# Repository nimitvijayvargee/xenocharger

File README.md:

# xenocharger
xenocharger is a compact 15.24mm x 15.24mm (0.6mil x 0.6mil) lipo charger and regulator packed with a ton of features! it can charge a battery 500mA, power projects up to 600mA on 3.3V, with features such as DPPM and trickle charging! It's powered by the BQ24030 IC and TP63001 from TI.

## PCB
the PCB is a compact 2 layer board that uses castellated holes to save even more spaces. 4 sets of headers are broken out, one for the battery, one for the input, one for the output and one for charge status.

## BOM
This is a rough BOM for the costs for this project. A PCB BOM can be found in pcb/prod/bom.csv, and the project BOM is just BOM.csv in the root of this repository.

ICs 
- TPS63001
- BQ24030

Other
- 1x BAT60A Diode

Passives
- 4x 100nF 0402
- 1x 1uF 0402
- 5x 10uF 0402
- 2x 22uF X7R 0402
- 1x 10kOhm 0402
- 1x 2.2kOhm 0402
- 1x 36kOhm 0402
- 1x 100Ohm 0402
- 1x SWPA3015S2R2MT 2.2uH

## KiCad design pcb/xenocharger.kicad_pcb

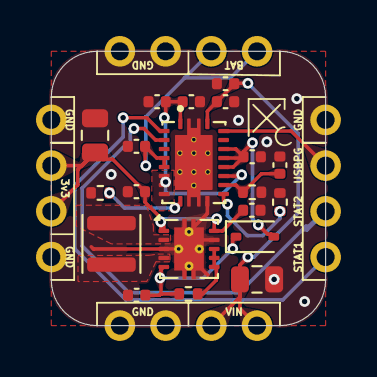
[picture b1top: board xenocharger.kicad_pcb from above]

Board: 2 copper layers, 15.2 x 15.2 mm, 24 parts (0 on the bottom side), 16 nets.

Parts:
C1, C2: X7R 22u; C_0805_2012Metric
C3, C4, C5, C9, C11: 10u; C_0402_1005Metric
C6, C7, C10, C12: 100n; C_0402_1005Metric
C8: 1u; C_0402_1005Metric
D2: BAT60A; D_SOD-323
J1, J2, J3, J4: Conn_01x04; PinHeader_1x04_P2.54mm_Vertical
L1: 2.2uH; L_Sunlord_SWPA3015S
R1: 100; R_0402_1005Metric
R2: 2.2k; R_0402_1005Metric
R4: 37k; R_0402_1005Metric
R5: 10k; R_0402_1005Metric
U2: BQ24030RHLR; IC_MSP430FR2522IRHLR
U3: TPS63001; Texas_DRC0010J_ThermalVias

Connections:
+3V3: C2.1, C4.1, C5.1, J3.2, J3.3, U3.1 (VOUT), U3.10 (FB)
/B+: C9.2, J4.3, J4.4, U2.5 (BAT), U2.6 (BAT)
/LDO: C7.2, C8.2, U2.1 (LDO), U2.7 (ISET2), U2.8 (PSEL), U2.9 (CE), U2.14 (TMR)
/R_ISET: R2.1, U2.10 (ISET1)
/STAT_1: J2.1, U2.2 (STAT1)
/STAT_2: J2.2, U2.3 (STAT2)
/USB_PG: J2.3, U2.19 (USBPG)
GND: C1.2, C2.2, C3.2, C4.2, C5.2, C6.1, C7.1, C8.1, C9.1, C10.1, C11.2, C12.1, J1.3, J1.4, J2.4, J3.1, J3.4, J4.1, J4.2, R2.2, R4.1, R5.1, U2.11 (VSS), U2.21 (EP), U3.3 (PGND), U3.9 (GND), U3.11 (PGND)
unnamed: C6.2, D2.2 (A), U2.15 (OUT), U2.16 (OUT), U2.17 (OUT)
unnamed: C3.1, D2.1 (K), R1.1, U3.5 (VIN)
unnamed: C10.2, R4.2, U2.13 (DPPM)
unnamed: R5.2, U2.12 (TS)
unnamed: R1.2, U3.6 (EN), U3.7 (PS/SYNC), U3.8 (VINA)
unnamed: L1.1, U3.4 (L1)
unnamed: L1.2, U3.2 (L2)
VBUS: C1.1, C11.1, C12.2, J1.1, J1.2, U2.20 (USB)

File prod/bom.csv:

Reference,Qty,Value,DNP,Exclude from BOM,Exclude from Board,Footprint,Datasheet,MANUFACTURER,MPN
"C1,C2",2,X7R 22u,,,,Capacitor_SMD:C_0805_2012Metric,,Robu.in,R233496
"C3,C4,C5,C9,C11",5,10u,,,,Capacitor_SMD:C_0402_1005Metric,,PCBPower,GPC0402106-6.3
"C6,C7,C10,C12",4,100n,,,,Capacitor_SMD:C_0402_1005Metric,,PCBPower,GPC0402104-50
C8,1,1u,,,,Capacitor_SMD:C_0402_1005Metric,,PCBPower,GPC0402105-16
D2,1,BAT60A,,,,Diode_SMD:D_SOD-323,https://www.infineon.com/dgdl/Infineon-BAT60ASERIES-DS-v01_0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,Robu.in,R242988
L1,1,2.2uH,,,,Inductor_SMD:L_Sunlord_SWPA4030S,,Robu.in,R114044
R1,1,100,,,,Resistor_SMD:R_0402_1005Metric,,Robu.in,R241093
R2,1,2.2k,,,,Resistor_SMD:R_0402_1005Metric,,PCBPower,GPR04022K2
R4,1,37k,,,,Resistor_SMD:R_0402_1005Metric,,Robu.in,R133843
R5,1,10k,,,,Resistor_SMD:R_0402_1005Metric,,PCBPower,GPR040210K
U2,1,BQ24030RHLR,,,,stuff:IC_MSP430FR2522IRHLR,http://www.ti.com/lit/gpn/bq24030,Robu.in,1086441
U3,1,TPS63001,,,,Package_SON:Texas_DRC0010J_ThermalVias,http://www.ti.com/lit/ds/symlink/tps63000.pdf,Mouser, 595-TPS63001DRCT
